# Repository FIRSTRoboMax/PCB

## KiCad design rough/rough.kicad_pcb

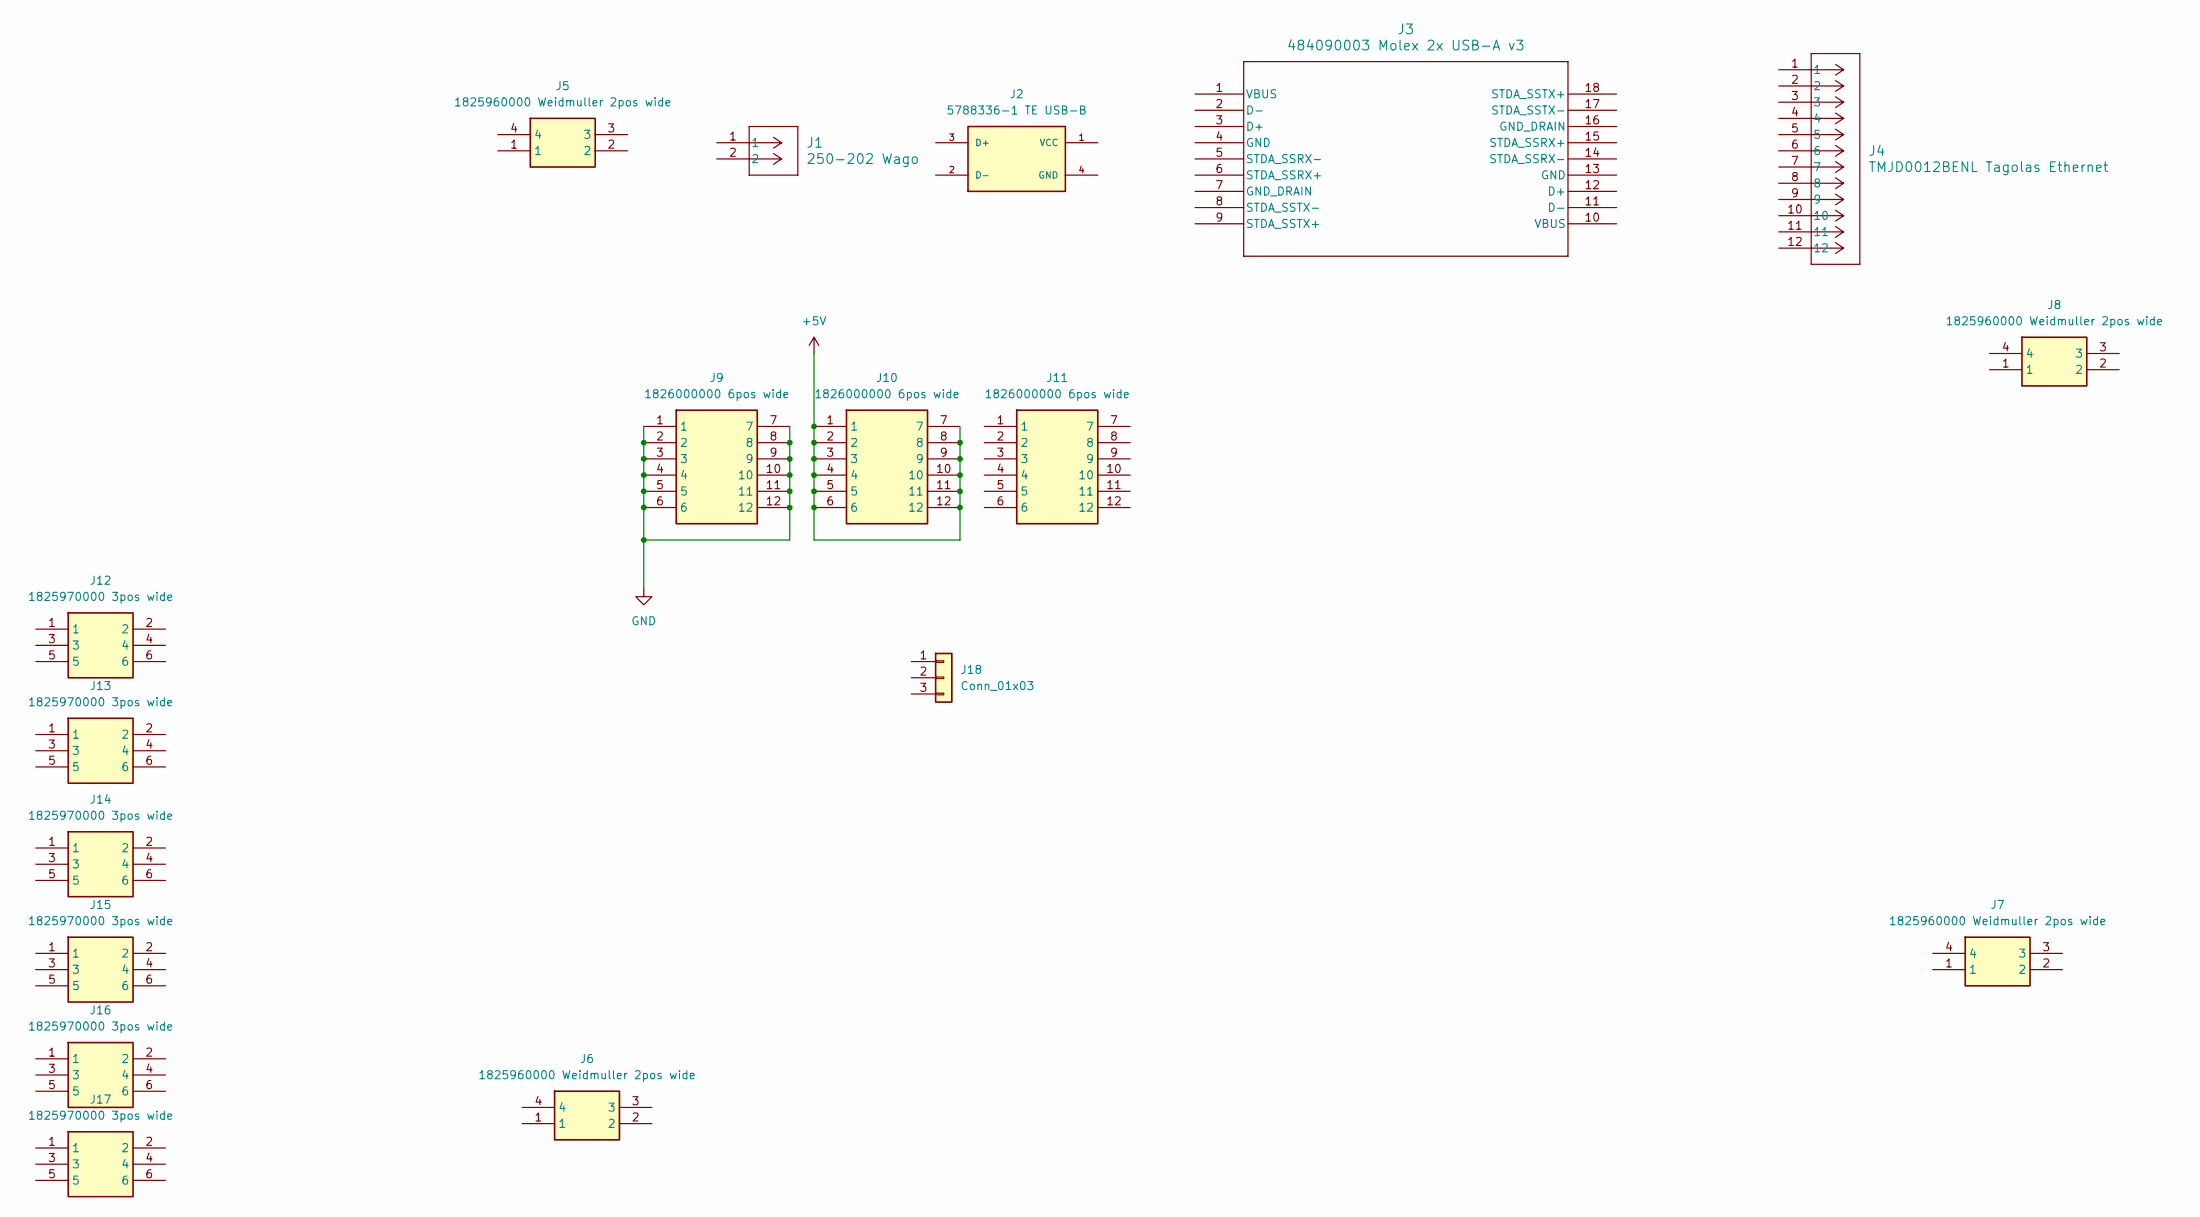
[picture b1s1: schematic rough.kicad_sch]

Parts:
J1: 250-202 Wago; CONN_250-202
J2: 5788336-1 TE USB-B; TE_5788336-1_USB-B; PARTREV R
J3: 484090003 Molex 2x USB-A v3; 48409-0003_MOL
J4: TMJD0012BENL Tagolas Ethernet; CONN12_0012BENL_TAL
J5, J6, J7, J8: 1825960000 Weidmuller 2pos wide; 1825960000; Manufacturer_Part_Number 1825960000; Mouser Part Number 470-1825960000
J9, J10, J11: 1826000000 6pos wide; 1826000000; Manufacturer_Part_Number 1826000000; Mouser Part Number 470-1826000000
J12, J13, J14, J15, J16, J17: 1825970000 3pos wide; 1825970000; Manufacturer_Part_Number 1825970000; Mouser Part Number 470-1825970000
J18: Conn_01x03

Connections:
+5V: J10.1, J10.2, J10.3, J10.4, J10.5, J10.6, J10.7, J10.8, J10.9, J10.10, J10.11, J10.12
GND: J9.1, J9.2, J9.3, J9.4, J9.5, J9.6, J9.7, J9.8, J9.9, J9.10, J9.11, J9.12

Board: 2 copper layers, 17 parts (0 on the bottom side), 2 nets, no tracks yet.

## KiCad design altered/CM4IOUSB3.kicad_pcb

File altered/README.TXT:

These files have been created in version 6 of KiCAD.

Some of the 3d models need to be downloaded form the following places and put into the CM4IO.3shapes directory some models are approximations.

https://datasheets.raspberrypi.org/cm4/CM4-step.zip
https://www.te.com/global-en/product-171826-4.html
https://www.molex.com/molex/products/part-detail/memory_card_socket/5033981892

The models provided in the 3dmodels directory are from various manufacturers including Diodes, Hirose, MTCONN, Toby, TRXCOM. Terms and conditions for the use of the models remain with the original manufacture.

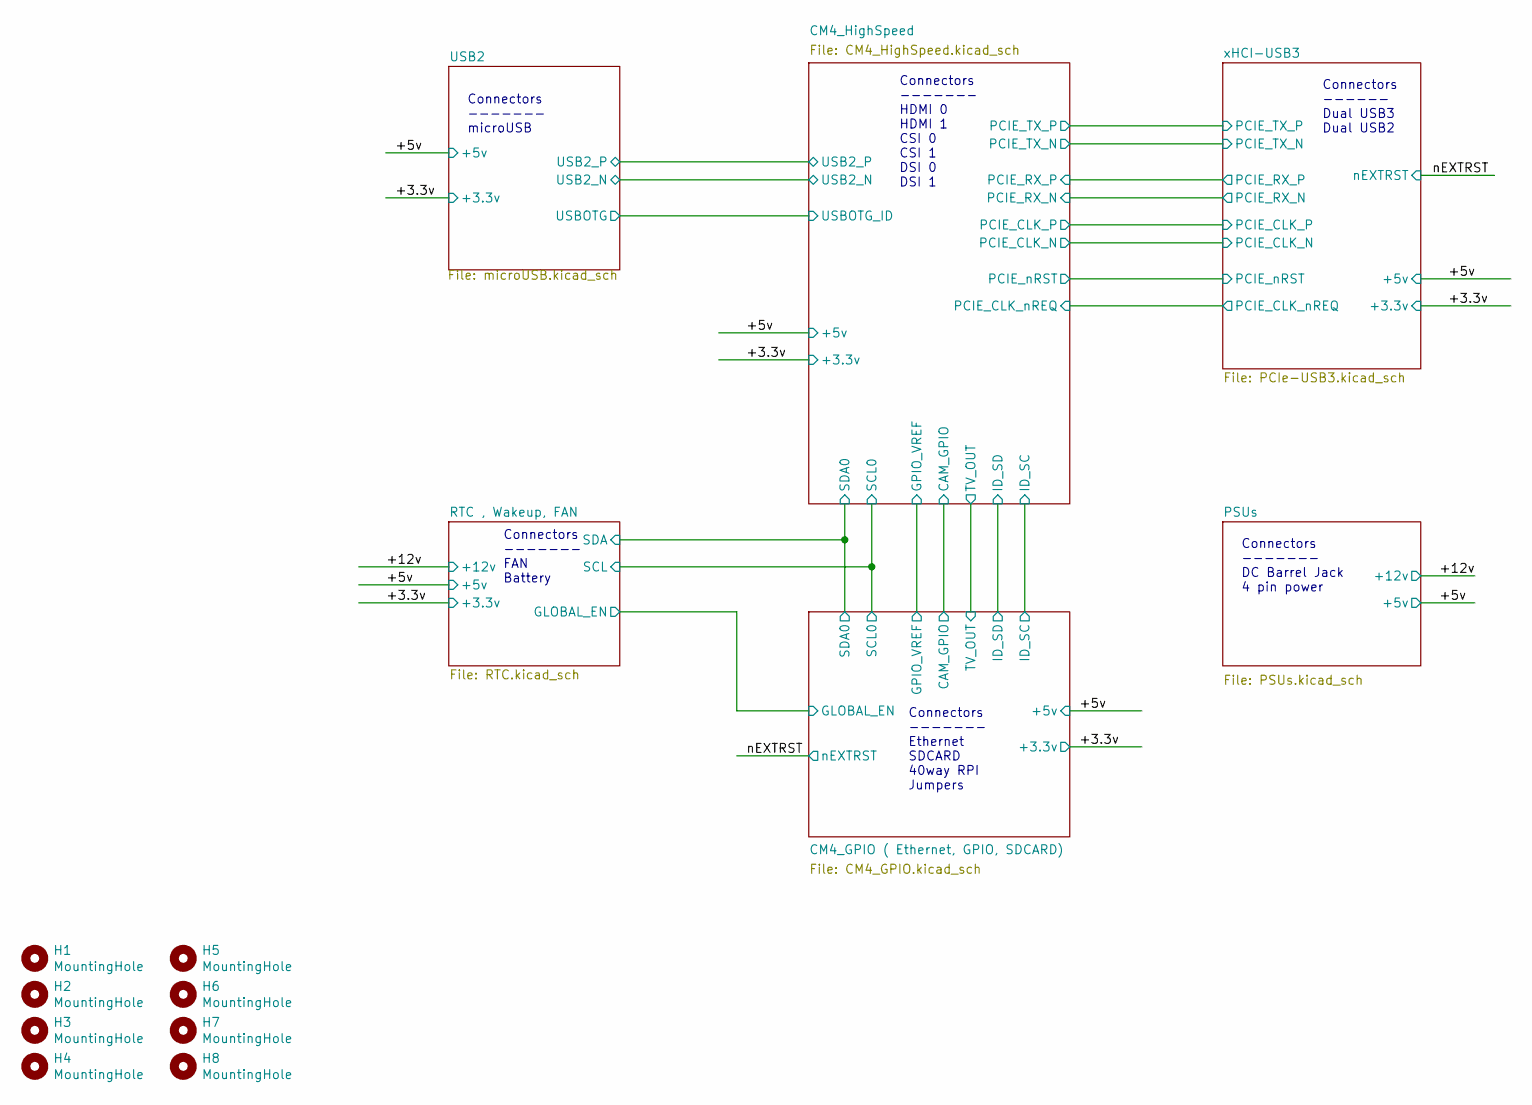
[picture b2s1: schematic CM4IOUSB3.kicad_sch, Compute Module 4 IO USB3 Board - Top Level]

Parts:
H1, H2, H3, H4, H5, H6, H7, H8: MountingHole; MountingHole_2.7mm_M2.5; Part Description M2.5 mounting hole

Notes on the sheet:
Connectors ------- microUSB
Connectors ------- DC Barrel Jack 4 pin power
Connectors ------- Ethernet SDCARD 40way RPI Jumpers
Connectors ------ Dual USB3 Dual USB2
Connectors ------- HDMI 0 HDMI 1 CSI 0 CSI 1 DSI 0 DSI 1
Connectors ------- FAN Battery

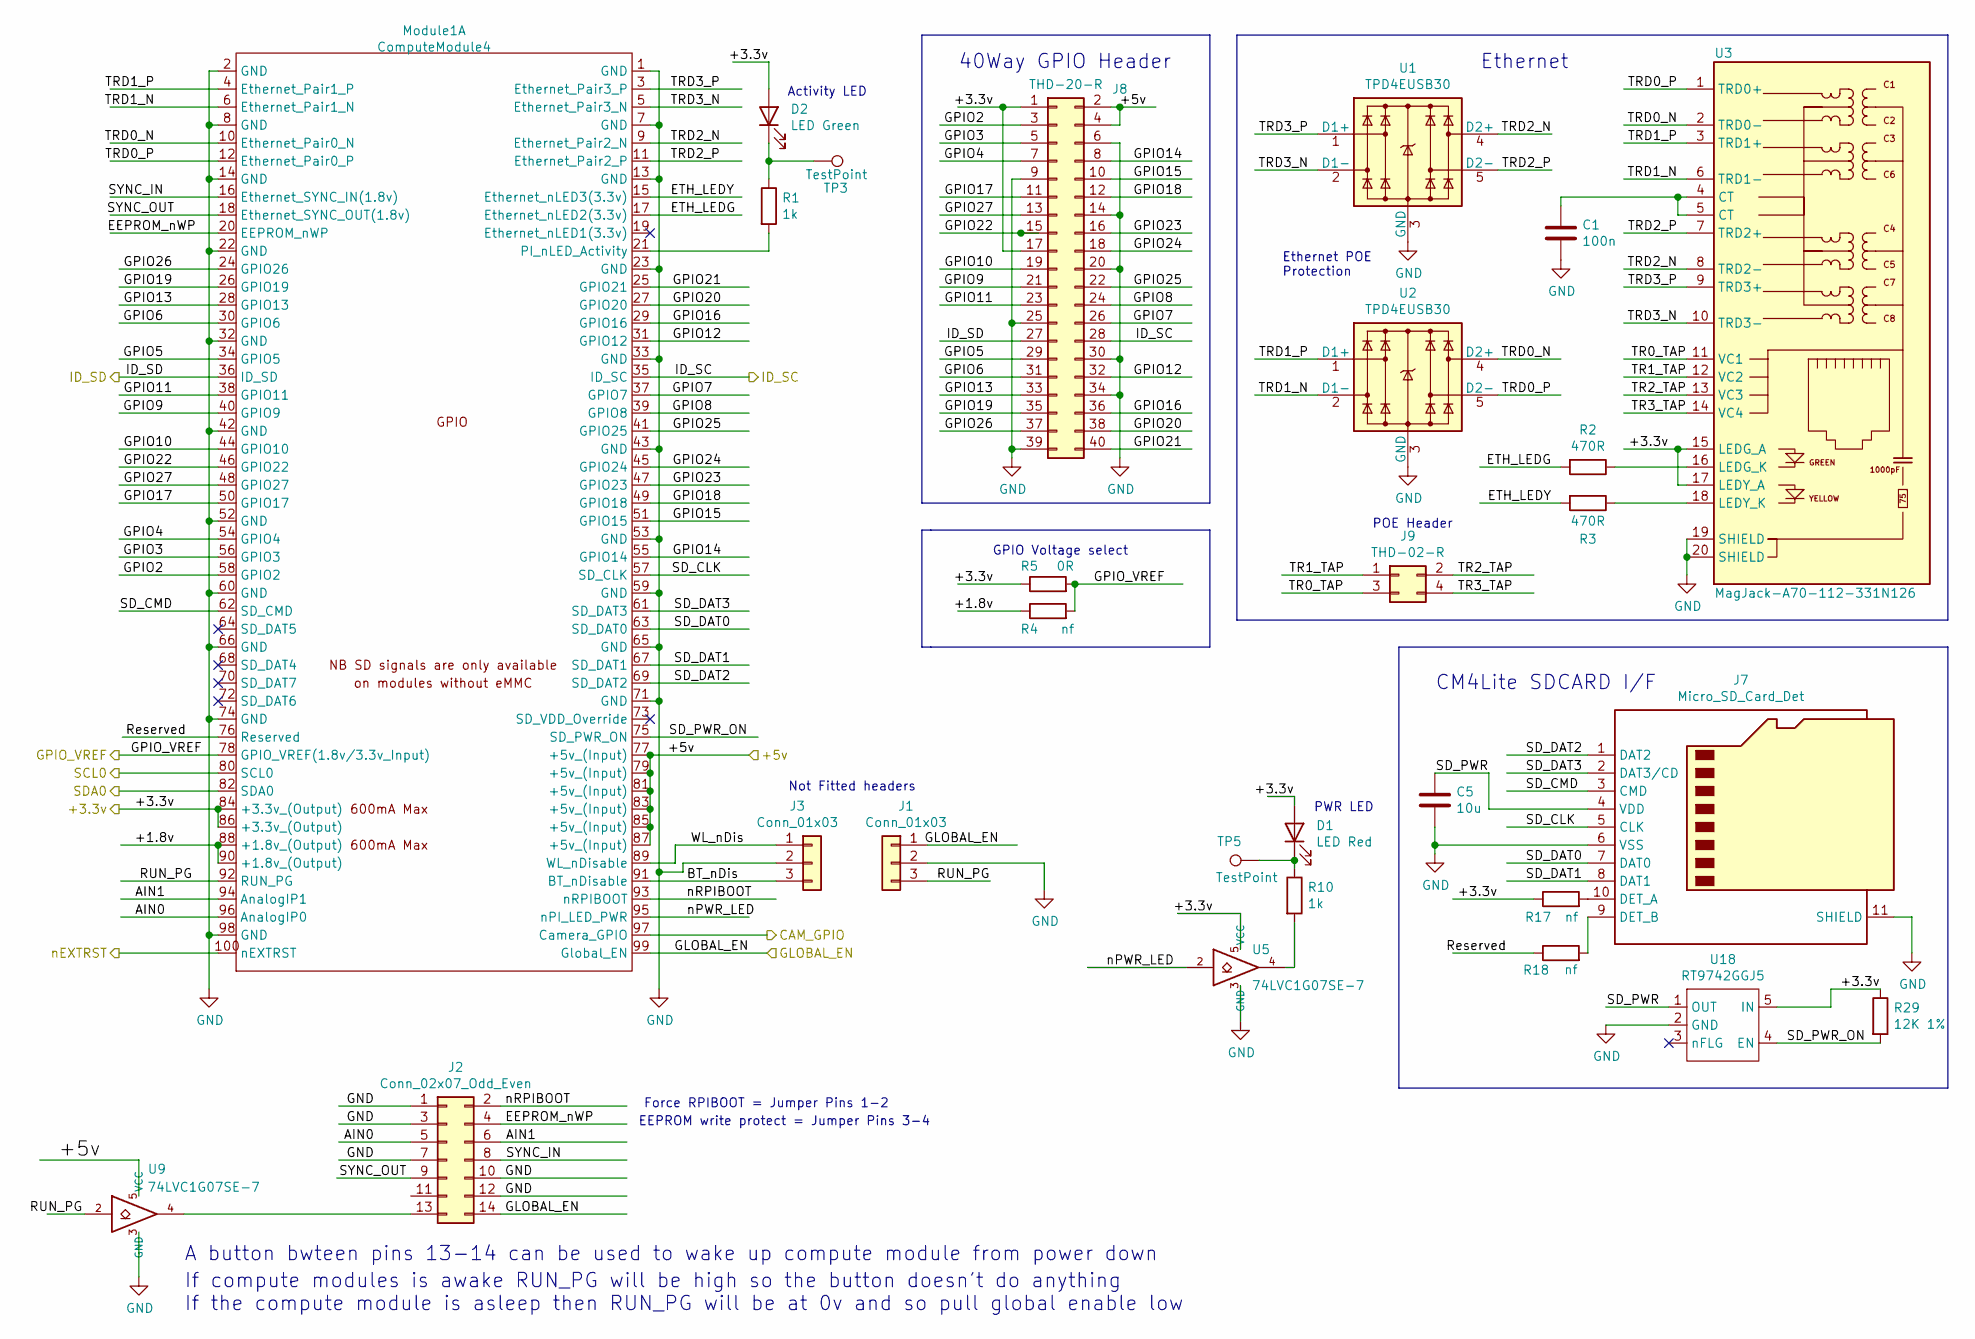
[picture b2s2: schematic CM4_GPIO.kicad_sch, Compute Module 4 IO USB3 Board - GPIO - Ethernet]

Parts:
C1: 100n; C_0402_1005Metric; Part Description 0.1uF 10% 16V Ceramic Capacitor X7R 040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
C5: 10u; C_0805_2012Metric; Part Description 10uF 10% 10V Ceramic Capacitor X7R 0805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
D1: LED Red; LED_0603_1608Metric; Part Description Red 620nm LED Indication - Discrete 2.2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
D2: LED Green; LED_0603_1608Metric; Part Description Green 572nm LED Indication - Discrete 2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
J1, J3: Conn_01x03; PinHeader_1x03_P2.54mm_Vertical; Part Description 3pin 0.1" connector
J2: Conn_02x07_Odd_Even; PinHeader_2x07_P2.54mm_Vertical; Part Description PinHeader_2x07_P2.54mm_Vertical
J7: Micro_SD_Card_Det; SDCARD_MOLEX_503398-1892; Part Description 9 (8 + 1) Position Card Connector micro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
J8: THD-20-R; PinHeader_2x20_P2.54mm_Vertical; Part Description PinHeader_2x20_P2.54mm_Vertical
J9: THD-02-R; PinHeader_2x02_P2.54mm_Vertical; Part Description PinHeader_2x02_P2.54mm_Vertical
Module1: ComputeModule4; Raspberry-Pi-4-Compute-Module; Part Description 100 Position Connector Receptacle, Cent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
R1, R10: 1k; R_0402_1005Metric; Part Description Resistor 1K M1005 1% 63mW
R2, R3: 470R; R_0402_1005Metric; Part Description Resistor 470R M1005 1% 63mW
R4: nf; R_0805_2012Metric_Pad1.15x1.40mm_HandSolder
R5: 0R; R_0805_2012Metric_Pad1.15x1.40mm_HandSolder; Part Description Resistor 0R M2012 5%
R17, R18: nf; R_0402_1005Metric; Part Description Resistor 1K M1005 1% 63mW
R29: 12K 1%; R_0402_1005Metric; Part Description Resistor 12K M1005 1% 63mW
TP3, TP5: TestPoint; TestPoint_Pad_2.0x2.0mm
U1, U2: TPD4EUSB30; USON-10_2.5x1.0mm_P0.5mm; Part Description Quad TVS diode for high speed signals (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
U3: MagJack-A70-112-331N126; TRJG0926HENL; Part Description Gigabit Ethernet Magjack
U5, U9: 74LVC1G07SE-7; SOT-353_SC-70-5; Part Description Buffer, Non-Inverting 1 Element 1 Bit p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
U18: RT9742GGJ5; SOT-23-5; Part Description Power Switch/Driver 1:1 N-Channel 1A TS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

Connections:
/+3.3v: D1.2 (A), D2.2 (A), J8.1, J8.17, Module1.84 (+3.3v_(Output)), Module1.86 (+3.3v_(Output)), R5.1, R17.1, R29.1, U3.15 (LEDG_A), U3.17 (LEDY_A), U5.5 (VCC), U18.5 (IN); also elsewhere on the board
/+5v: J8.2, J8.4, Module1.77 (+5v_(Input)), Module1.79 (+5v_(Input)), Module1.81 (+5v_(Input)), Module1.83 (+5v_(Input)), Module1.85 (+5v_(Input)), Module1.87 (+5v_(Input)), U9.5 (VCC); also elsewhere on the board
/CM4_GPIO ( Ethernet, GPIO, SDCARD)/+1.8v: Module1.88 (+1.8v_(Output)), Module1.90 (+1.8v_(Output)), R4.1
/CM4_GPIO ( Ethernet, GPIO, SDCARD)/AIN0: J2.5, Module1.96 (AnalogIP0)
/CM4_GPIO ( Ethernet, GPIO, SDCARD)/AIN1: J2.6, Module1.94 (AnalogIP1)
/CM4_GPIO ( Ethernet, GPIO, SDCARD)/BT_nDis: J3.3, Module1.91 (BT_nDisable)
/CM4_GPIO ( Ethernet, GPIO, SDCARD)/CAM_GPIO: Module1.97 (Camera_GPIO)
/CM4_GPIO ( Ethernet, GPIO, SDCARD)/EEPROM_nWP: J2.4, Module1.20 (EEPROM_nWP)
/CM4_GPIO ( Ethernet, GPIO, SDCARD)/ETH_LEDG: Module1.17 (Ethernet_nLED2(3.3v)), R2.2
/CM4_GPIO ( Ethernet, GPIO, SDCARD)/ETH_LEDY: Module1.15 (Ethernet_nLED3(3.3v)), R3.2
/CM4_GPIO ( Ethernet, GPIO, SDCARD)/GLOBAL_EN: J1.1, J2.14, Module1.99 (Global_EN); also elsewhere on the board
/CM4_GPIO ( Ethernet, GPIO, SDCARD)/GPIO2: J8.3, Module1.58 (GPIO2)
/CM4_GPIO ( Ethernet, GPIO, SDCARD)/GPIO3: J8.5, Module1.56 (GPIO3)
/CM4_GPIO ( Ethernet, GPIO, SDCARD)/GPIO4: J8.7, Module1.54 (GPIO4)
/CM4_GPIO ( Ethernet, GPIO, SDCARD)/GPIO5: J8.29, Module1.34 (GPIO5)
/CM4_GPIO ( Ethernet, GPIO, SDCARD)/GPIO6: J8.31, Module1.30 (GPIO6)
/CM4_GPIO ( Ethernet, GPIO, SDCARD)/GPIO7: J8.26, Module1.37 (GPIO7)
/CM4_GPIO ( Ethernet, GPIO, SDCARD)/GPIO8: J8.24, Module1.39 (GPIO8)
/CM4_GPIO ( Ethernet, GPIO, SDCARD)/GPIO9: J8.21, Module1.40 (GPIO9)
/CM4_GPIO ( Ethernet, GPIO, SDCARD)/GPIO10: J8.19, Module1.44 (GPIO10)
/CM4_GPIO ( Ethernet, GPIO, SDCARD)/GPIO11: J8.23, Module1.38 (GPIO11)
/CM4_GPIO ( Ethernet, GPIO, SDCARD)/GPIO12: J8.32, Module1.31 (GPIO12)
/CM4_GPIO ( Ethernet, GPIO, SDCARD)/GPIO13: J8.33, Module1.28 (GPIO13)
/CM4_GPIO ( Ethernet, GPIO, SDCARD)/GPIO14: J8.8, Module1.55 (GPIO14)
/CM4_GPIO ( Ethernet, GPIO, SDCARD)/GPIO15: J8.10, Module1.51 (GPIO15)
/CM4_GPIO ( Ethernet, GPIO, SDCARD)/GPIO16: J8.36, Module1.29 (GPIO16)
/CM4_GPIO ( Ethernet, GPIO, SDCARD)/GPIO17: J8.11, Module1.50 (GPIO17)
/CM4_GPIO ( Ethernet, GPIO, SDCARD)/GPIO18: J8.12, Module1.49 (GPIO18)
/CM4_GPIO ( Ethernet, GPIO, SDCARD)/GPIO19: J8.35, Module1.26 (GPIO19)
/CM4_GPIO ( Ethernet, GPIO, SDCARD)/GPIO20: J8.38, Module1.27 (GPIO20)
/CM4_GPIO ( Ethernet, GPIO, SDCARD)/GPIO21: J8.40, Module1.25 (GPIO21)
/CM4_GPIO ( Ethernet, GPIO, SDCARD)/GPIO22: J8.15, Module1.46 (GPIO22)
/CM4_GPIO ( Ethernet, GPIO, SDCARD)/GPIO23: J8.16, Module1.47 (GPIO23)
/CM4_GPIO ( Ethernet, GPIO, SDCARD)/GPIO24: J8.18, Module1.45 (GPIO24)
/CM4_GPIO ( Ethernet, GPIO, SDCARD)/GPIO25: J8.22, Module1.41 (GPIO25)
/CM4_GPIO ( Ethernet, GPIO, SDCARD)/GPIO26: J8.37, Module1.24 (GPIO26)
/CM4_GPIO ( Ethernet, GPIO, SDCARD)/GPIO27: J8.13, Module1.48 (GPIO27)
/CM4_GPIO ( Ethernet, GPIO, SDCARD)/GPIO_VREF: Module1.78 (GPIO_VREF(1.8v/3.3v_Input)), R4.2, R5.2
/CM4_GPIO ( Ethernet, GPIO, SDCARD)/ID_SC: J8.28, Module1.35 (ID_SC)
/CM4_GPIO ( Ethernet, GPIO, SDCARD)/ID_SD: J8.27, Module1.36 (ID_SD)
/CM4_GPIO ( Ethernet, GPIO, SDCARD)/RUN_PG: J1.3, Module1.92 (RUN_PG), U9.2
/CM4_GPIO ( Ethernet, GPIO, SDCARD)/Reserved: Module1.76 (Reserved), R18.1
/CM4_GPIO ( Ethernet, GPIO, SDCARD)/SD_CLK: J7.5 (CLK), Module1.57 (SD_CLK)
/CM4_GPIO ( Ethernet, GPIO, SDCARD)/SD_CMD: J7.3 (CMD), Module1.62 (SD_CMD)
/CM4_GPIO ( Ethernet, GPIO, SDCARD)/SD_DAT0: J7.7 (DAT0), Module1.63 (SD_DAT0)
/CM4_GPIO ( Ethernet, GPIO, SDCARD)/SD_DAT1: J7.8 (DAT1), Module1.67 (SD_DAT1)
/CM4_GPIO ( Ethernet, GPIO, SDCARD)/SD_DAT2: J7.1 (DAT2), Module1.69 (SD_DAT2)
/CM4_GPIO ( Ethernet, GPIO, SDCARD)/SD_DAT3: J7.2 (DAT3/CD), Module1.61 (SD_DAT3)
/CM4_GPIO ( Ethernet, GPIO, SDCARD)/SD_PWR: C5.1, J7.4 (VDD), U18.1 (OUT)
/CM4_GPIO ( Ethernet, GPIO, SDCARD)/SD_PWR_ON: Module1.75 (SD_PWR_ON), R29.2, U18.4 (EN)
/CM4_GPIO ( Ethernet, GPIO, SDCARD)/SYNC_IN: J2.8, Module1.16 (Ethernet_SYNC_IN(1.8v))
/CM4_GPIO ( Ethernet, GPIO, SDCARD)/SYNC_OUT: J2.9, Module1.18 (Ethernet_SYNC_OUT(1.8v))
/CM4_GPIO ( Ethernet, GPIO, SDCARD)/TR0_TAP: J9.3, U3.11 (VC1)
/CM4_GPIO ( Ethernet, GPIO, SDCARD)/TR1_TAP: J9.1, U3.12 (VC2)
/CM4_GPIO ( Ethernet, GPIO, SDCARD)/TR2_TAP: J9.2, U3.13 (VC3)
/CM4_GPIO ( Ethernet, GPIO, SDCARD)/TR3_TAP: J9.4, U3.14 (VC4)
/CM4_GPIO ( Ethernet, GPIO, SDCARD)/TRD0_N: Module1.10 (Ethernet_Pair0_N), U2.4 (D2+), U2.7, U3.2 (TRD0-)
/CM4_GPIO ( Ethernet, GPIO, SDCARD)/TRD0_P: Module1.12 (Ethernet_Pair0_P), U2.5 (D2-), U2.6, U3.1 (TRD0+)
/CM4_GPIO ( Ethernet, GPIO, SDCARD)/TRD1_N: Module1.6 (Ethernet_Pair1_N), U2.2 (D1-), U2.9, U3.6 (TRD1-)
/CM4_GPIO ( Ethernet, GPIO, SDCARD)/TRD1_P: Module1.4 (Ethernet_Pair1_P), U2.1 (D1+), U2.10, U3.3 (TRD1+)
/CM4_GPIO ( Ethernet, GPIO, SDCARD)/TRD2_N: Module1.9 (Ethernet_Pair2_N), U1.4 (D2+), U1.7, U3.8 (TRD2-)
/CM4_GPIO ( Ethernet, GPIO, SDCARD)/TRD2_P: Module1.11 (Ethernet_Pair2_P), U1.5 (D2-), U1.6, U3.7 (TRD2+)
/CM4_GPIO ( Ethernet, GPIO, SDCARD)/TRD3_N: Module1.5 (Ethernet_Pair3_N), U1.2 (D1-), U1.9, U3.10 (TRD3-)
/CM4_GPIO ( Ethernet, GPIO, SDCARD)/TRD3_P: Module1.3 (Ethernet_Pair3_P), U1.1 (D1+), U1.10, U3.9 (TRD3+)
/CM4_GPIO ( Ethernet, GPIO, SDCARD)/WL_nDis: J3.1, Module1.89 (WL_nDisable)
/CM4_GPIO ( Ethernet, GPIO, SDCARD)/nPWR_LED: Module1.95 (nPI_LED_PWR), U5.2
/CM4_GPIO ( Ethernet, GPIO, SDCARD)/nRPIBOOT: J2.2, Module1.93 (nRPIBOOT)
/RTC , Wakeup, FAN/SCL: Module1.80 (SCL0); also elsewhere on the board
/RTC , Wakeup, FAN/SDA: Module1.82 (SDA0); also elsewhere on the board
/nEXTRST: Module1.100 (nEXTRST); also elsewhere on the board
GND: C1.2, C5.2, J1.2, J2.1, J2.3, J2.7, J2.10, J2.12, J3.2, J7.6 (VSS), J7.11 (SHIELD), J8.6, J8.9, J8.14, J8.20, J8.25, J8.30, J8.34, J8.39, Module1.1 (GND), Module1.2 (GND), Module1.7 (GND), Module1.8 (GND), Module1.13 (GND), Module1.14 (GND), Module1.22 (GND), Module1.23 (GND), Module1.32 (GND), Module1.33 (GND), Module1.42 (GND), Module1.43 (GND), Module1.52 (GND), Module1.53 (GND), Module1.59 (GND), Module1.60 (GND), Module1.65 (GND), Module1.66 (GND), Module1.71 (GND), Module1.74 (GND), Module1.98 (GND), U1.3 (GND), U1.8 (GND), U2.3 (GND), U2.8 (GND), U3.19 (SHIELD), U3.20 (SHIELD), U5.3 (GND), U9.3 (GND), U18.2 (GND); also elsewhere on the board
unnamed: C1.1, U3.4 (CT), U3.5 (CT)
unnamed: D1.1 (K), R10.1, TP5.1
unnamed: D2.1 (K), R1.1, TP3.1
unnamed: J2.13, U9.4
unnamed: J7.10 (DET_A), R17.2
unnamed: J7.9 (DET_B), R18.2
unnamed: Module1.21 (PI_nLED_Activity), R1.2
unnamed: R10.2, U5.4
unnamed: R2.1, U3.16 (LEDG_K)
unnamed: R3.1, U3.18 (LEDY_K)

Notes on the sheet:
40Way GPIO Header
Activity LED
Ethernet POE Protection
GPIO Voltage select
EEPROM write protect = Jumper Pins 3-4
Not Fitted headers
POE Header
Force RPIBOOT = Jumper Pins 1-2
PWR LED
A button bwteen pins 13-14 can be used to wake up compute module from power down
Ethernet
If compute modules is awake RUN_PG will be high so the button doesn't do anything If the compute module is asleep then RUN_PG will be at 0v and so pull global enable low
CM4Lite SDCARD I/F

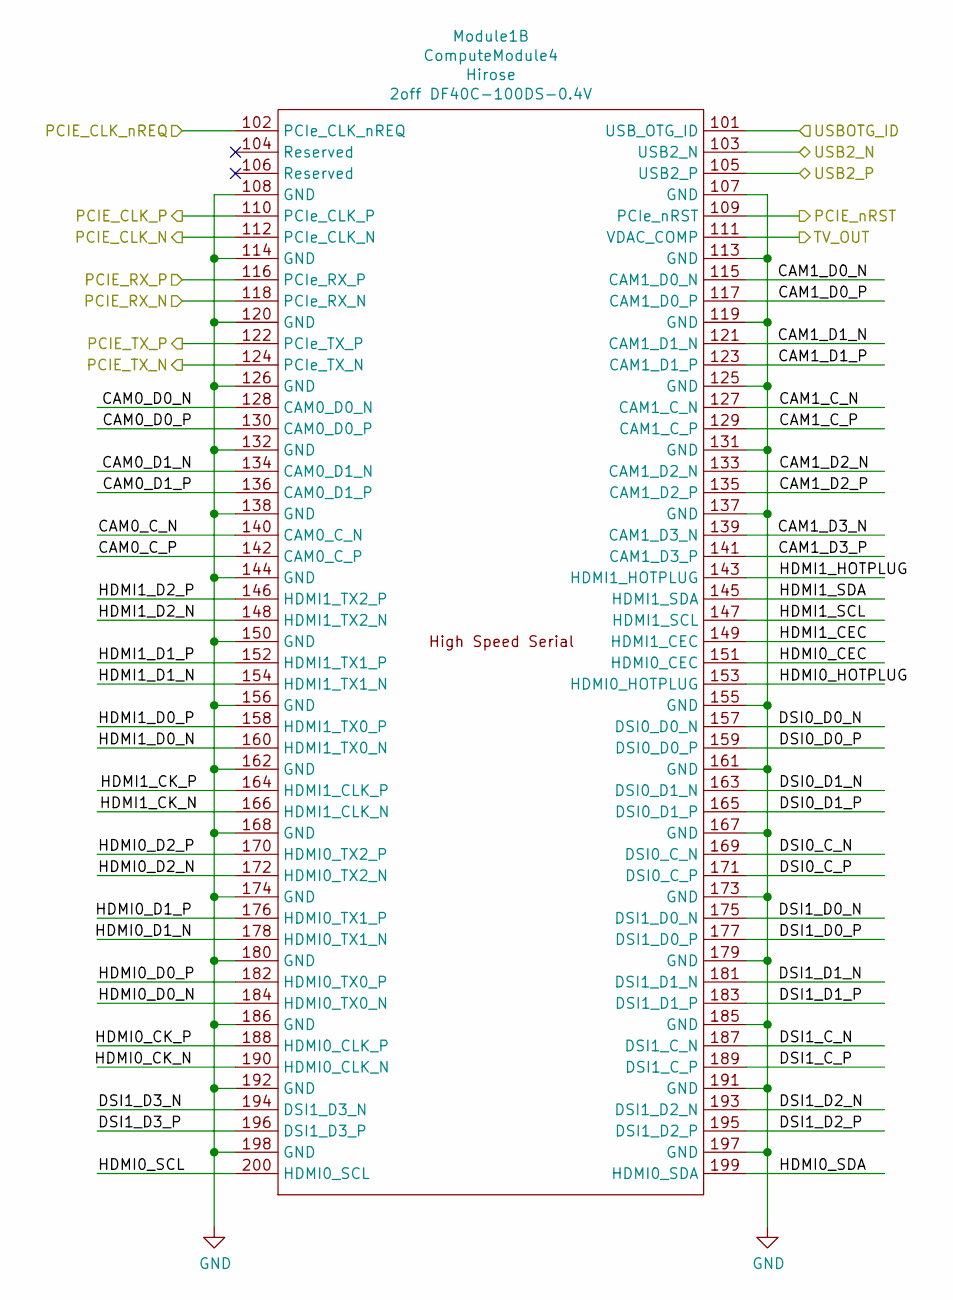
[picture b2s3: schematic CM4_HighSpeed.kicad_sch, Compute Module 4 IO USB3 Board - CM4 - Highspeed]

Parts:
Module1: ComputeModule4; Raspberry-Pi-4-Compute-Module; Part Description 100 Position Connector Receptacle, Cent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

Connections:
/CM4_HighSpeed/CAM0_C_N: Module1.140 (CAM0_C_N)
/CM4_HighSpeed/CAM0_C_P: Module1.142 (CAM0_C_P)
/CM4_HighSpeed/CAM0_D0_N: Module1.128 (CAM0_D0_N)
/CM4_HighSpeed/CAM0_D0_P: Module1.130 (CAM0_D0_P)
/CM4_HighSpeed/CAM0_D1_N: Module1.134 (CAM0_D1_N)
/CM4_HighSpeed/CAM0_D1_P: Module1.136 (CAM0_D1_P)
/CM4_HighSpeed/CAM1_C_N: Module1.127 (CAM1_C_N)
/CM4_HighSpeed/CAM1_C_P: Module1.129 (CAM1_C_P)
/CM4_HighSpeed/CAM1_D0_N: Module1.115 (CAM1_D0_N)
/CM4_HighSpeed/CAM1_D0_P: Module1.117 (CAM1_D0_P)
/CM4_HighSpeed/CAM1_D1_N: Module1.121 (CAM1_D1_N)
/CM4_HighSpeed/CAM1_D1_P: Module1.123 (CAM1_D1_P)
/CM4_HighSpeed/CAM1_D2_N: Module1.133 (CAM1_D2_N)
/CM4_HighSpeed/CAM1_D2_P: Module1.135 (CAM1_D2_P)
/CM4_HighSpeed/CAM1_D3_N: Module1.139 (CAM1_D3_N)
/CM4_HighSpeed/CAM1_D3_P: Module1.141 (CAM1_D3_P)
/CM4_HighSpeed/DSI0_C_N: Module1.169 (DSI0_C_N)
/CM4_HighSpeed/DSI0_C_P: Module1.171 (DSI0_C_P)
/CM4_HighSpeed/DSI0_D0_N: Module1.157 (DSI0_D0_N)
/CM4_HighSpeed/DSI0_D0_P: Module1.159 (DSI0_D0_P)
/CM4_HighSpeed/DSI0_D1_N: Module1.163 (DSI0_D1_N)
/CM4_HighSpeed/DSI0_D1_P: Module1.165 (DSI0_D1_P)
/CM4_HighSpeed/DSI1_C_N: Module1.187 (DSI1_C_N)
/CM4_HighSpeed/DSI1_C_P: Module1.189 (DSI1_C_P)
/CM4_HighSpeed/DSI1_D0_N: Module1.175 (DSI1_D0_N)
/CM4_HighSpeed/DSI1_D0_P: Module1.177 (DSI1_D0_P)
/CM4_HighSpeed/DSI1_D1_N: Module1.181 (DSI1_D1_N)
/CM4_HighSpeed/DSI1_D1_P: Module1.183 (DSI1_D1_P)
/CM4_HighSpeed/DSI1_D2_N: Module1.193 (DSI1_D2_N)
/CM4_HighSpeed/DSI1_D2_P: Module1.195 (DSI1_D2_P)
/CM4_HighSpeed/DSI1_D3_N: Module1.194 (DSI1_D3_N)
/CM4_HighSpeed/DSI1_D3_P: Module1.196 (DSI1_D3_P)
/CM4_HighSpeed/HDMI0_CEC: Module1.151 (HDMI0_CEC)
/CM4_HighSpeed/HDMI0_CK_N: Module1.190 (HDMI0_CLK_N)
/CM4_HighSpeed/HDMI0_CK_P: Module1.188 (HDMI0_CLK_P)
/CM4_HighSpeed/HDMI0_D0_N: Module1.184 (HDMI0_TX0_N)
/CM4_HighSpeed/HDMI0_D0_P: Module1.182 (HDMI0_TX0_P)
/CM4_HighSpeed/HDMI0_D1_N: Module1.178 (HDMI0_TX1_N)
/CM4_HighSpeed/HDMI0_D1_P: Module1.176 (HDMI0_TX1_P)
/CM4_HighSpeed/HDMI0_D2_N: Module1.172 (HDMI0_TX2_N)
/CM4_HighSpeed/HDMI0_D2_P: Module1.170 (HDMI0_TX2_P)
/CM4_HighSpeed/HDMI0_HOTPLUG: Module1.153 (HDMI0_HOTPLUG)
/CM4_HighSpeed/HDMI0_SCL: Module1.200 (HDMI0_SCL)
/CM4_HighSpeed/HDMI0_SDA: Module1.199 (HDMI0_SDA)
/CM4_HighSpeed/HDMI1_CEC: Module1.149 (HDMI1_CEC)
/CM4_HighSpeed/HDMI1_CK_N: Module1.166 (HDMI1_CLK_N)
/CM4_HighSpeed/HDMI1_CK_P: Module1.164 (HDMI1_CLK_P)
/CM4_HighSpeed/HDMI1_D0_N: Module1.160 (HDMI1_TX0_N)
/CM4_HighSpeed/HDMI1_D0_P: Module1.158 (HDMI1_TX0_P)
/CM4_HighSpeed/HDMI1_D1_N: Module1.154 (HDMI1_TX1_N)
/CM4_HighSpeed/HDMI1_D1_P: Module1.152 (HDMI1_TX1_P)
/CM4_HighSpeed/HDMI1_D2_N: Module1.148 (HDMI1_TX2_N)
/CM4_HighSpeed/HDMI1_D2_P: Module1.146 (HDMI1_TX2_P)
/CM4_HighSpeed/HDMI1_HOTPLUG: Module1.143 (HDMI1_HOTPLUG)
/CM4_HighSpeed/HDMI1_SCL: Module1.147 (HDMI1_SCL)
/CM4_HighSpeed/HDMI1_SDA: Module1.145 (HDMI1_SDA)
/CM4_HighSpeed/PCIE_CLK_N: Module1.112 (PCIe_CLK_N); also elsewhere on the board
/CM4_HighSpeed/PCIE_CLK_P: Module1.110 (PCIe_CLK_P); also elsewhere on the board
/CM4_HighSpeed/PCIE_CLK_nREQ: Module1.102 (PCIe_CLK_nREQ); also elsewhere on the board
/CM4_HighSpeed/PCIE_RX_N: Module1.118 (PCIe_RX_N); also elsewhere on the board
/CM4_HighSpeed/PCIE_RX_P: Module1.116 (PCIe_RX_P); also elsewhere on the board
/CM4_HighSpeed/PCIE_TX_N: Module1.124 (PCIe_TX_N); also elsewhere on the board
/CM4_HighSpeed/PCIE_TX_P: Module1.122 (PCIe_TX_P); also elsewhere on the board
/CM4_HighSpeed/PCIE_nRST: Module1.109 (PCIe_nRST); also elsewhere on the board
/CM4_HighSpeed/TV_OUT: Module1.111 (VDAC_COMP)
/CM4_HighSpeed/USBOTG_ID: Module1.101 (USB_OTG_ID); also elsewhere on the board
/USB2/USBD_N: Module1.103 (USB2_N); also elsewhere on the board
/USB2/USBD_P: Module1.105 (USB2_P); also elsewhere on the board
GND: Module1.107 (GND), Module1.108 (GND), Module1.113 (GND), Module1.114 (GND), Module1.119 (GND), Module1.120 (GND), Module1.125 (GND), Module1.126 (GND), Module1.131 (GND), Module1.132 (GND), Module1.137 (GND), Module1.138 (GND), Module1.144 (GND), Module1.150 (GND), Module1.155 (GND), Module1.156 (GND), Module1.161 (GND), Module1.162 (GND), Module1.167 (GND), Module1.168 (GND), Module1.173 (GND), Module1.174 (GND), Module1.179 (GND), Module1.180 (GND), Module1.185 (GND), Module1.186 (GND), Module1.191 (GND), Module1.192 (GND), Module1.197 (GND), Module1.198 (GND); also elsewhere on the board

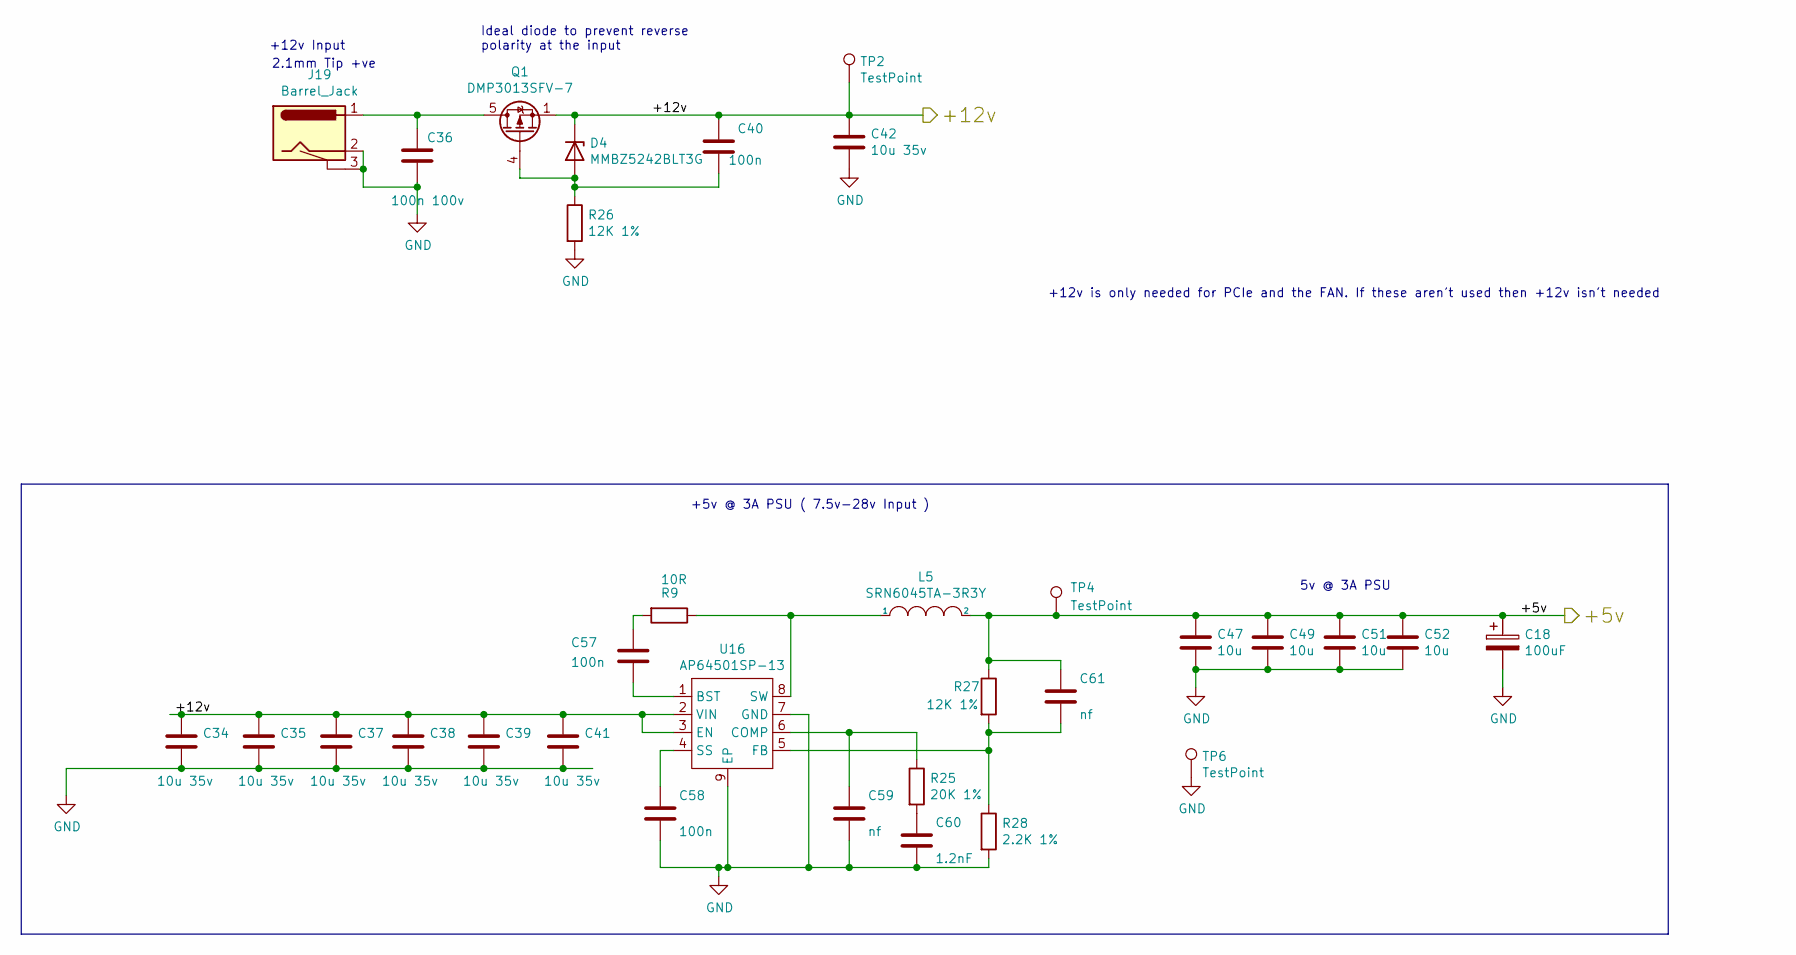
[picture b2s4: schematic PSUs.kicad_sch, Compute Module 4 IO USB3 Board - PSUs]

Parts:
C18: 100uF; CP_EIA-7343-31_Kemet-D; Part Description Capacitor, SP-Cap, 100u, 6.3V, 15mR ESR
C34, C35, C37, C38, C39, C41, C42: 10u 35v; C_0805_2012Metric; Part Description 10uF 10% or 20% 35V Ceramic Capacitor X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
C36: 100n 100v; C_0402_1005Metric; Part Description 0.1uF 10% 100V Ceramic Capacitor X5R 04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
C40, C57, C58: 100n; C_0402_1005Metric; Part Description 0.1uF 10% 16V Ceramic Capacitor X7R 040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
C47, C49, C51, C52: 10u; C_0805_2012Metric; Part Description 10uF 10% 10V Ceramic Capacitor X7R 0805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
C59: nf; C_0402_1005Metric
C60: 1.2nF; C_0402_1005Metric; Part Description 1200pF 10% 10V Ceramic Capacitor X5R 04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
C61: nf; C_0402_1005Metric; Part Description 220 pF, 50 V, 0402 [1005 Metric], ± 5%,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
D4: MMBZ5242BLT3G; D_SOT-23_ANK; Part Description Zener Diode 12V 225mW 5% Surface Mount 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
J19: Barrel_Jack; BarrelJack_Horizontal; Part Description DC Power Connectors PCB 2.1MM
L5: SRN6045TA-3R3Y; L_Bourns_SRN6045TA; Part Description 3.3µH Semi-Shielded Wirewound Inductor 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
Q1: DMP3013SFV-7; Diodes_PowerDI3333-8; Part Description DMP3013SFV-7 - Power MOSFET, P Channel,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
R9: 10R; R_0402_1005Metric; Part Description Resistor 10R M1005 1% 63mW
R25: 20K 1%; R_0402_1005Metric; Part Description Resistor 20K M1005 1% 63mW
R26, R27: 12K 1%; R_0402_1005Metric; Part Description Resistor 12K M1005 1% 63mW
R28: 2.2K 1%; R_0402_1005Metric; Part Description Resistor 2.2K M1005 1% 63mW
TP2, TP4, TP6: TestPoint; TestPoint_Pad_2.0x2.0mm
U16: AP64501SP-13; SOIC-8-1EP_3.9x4.9mm_P1.27mm_EP2.95x4.9mm_Mask2.71x3.4mm_Th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; Part Description Buck Switching Regulator IC Positive Ad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

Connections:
/+5v: C18.1, C47.1, C49.1, C51.1, C52.1, C61.1, L5.2, R27.1, TP4.1; also elsewhere on the board
/+12v: C34.1, C35.1, C37.1, C38.1, C39.1, C40.1, C41.1, C42.1, D4.1 (K), Q1.1 (S), Q1.2 (S), Q1.3 (S), TP2.1, U16.2 (VIN), U16.3 (EN)
GND: C18.2, C34.2, C35.2, C36.2, C37.2, C38.2, C39.2, C41.2, C42.2, C47.2, C49.2, C51.2, C52.2, C58.2, C59.2, C60.2, J19.2, J19.3, R26.2, R28.2, TP6.1, U16.7 (GND), U16.9 (EP); also elsewhere on the board
unnamed: C57.1, R9.2
unnamed: C60.1, R25.2
unnamed: C40.2, D4.2 (A), Q1.4 (G), R26.1
unnamed: C36.1, J19.1, Q1.5 (D)
unnamed: C57.2, U16.1 (BST)
unnamed: C59.1, R25.1, U16.6 (COMP)
unnamed: C61.2, R27.2, R28.1, U16.5 (FB)
unnamed: C58.1, U16.4 (SS)
unnamed: L5.1, R9.1, U16.8 (SW)

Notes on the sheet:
+5v @ 3A PSU ( 7.5v-28v Input )
+12v is only needed for PCIe and the FAN. If these aren't used then +12v isn't needed
Ideal diode to prevent reverse polarity at the input
+12v Input
2.1mm Tip +ve
5v @ 3A PSU

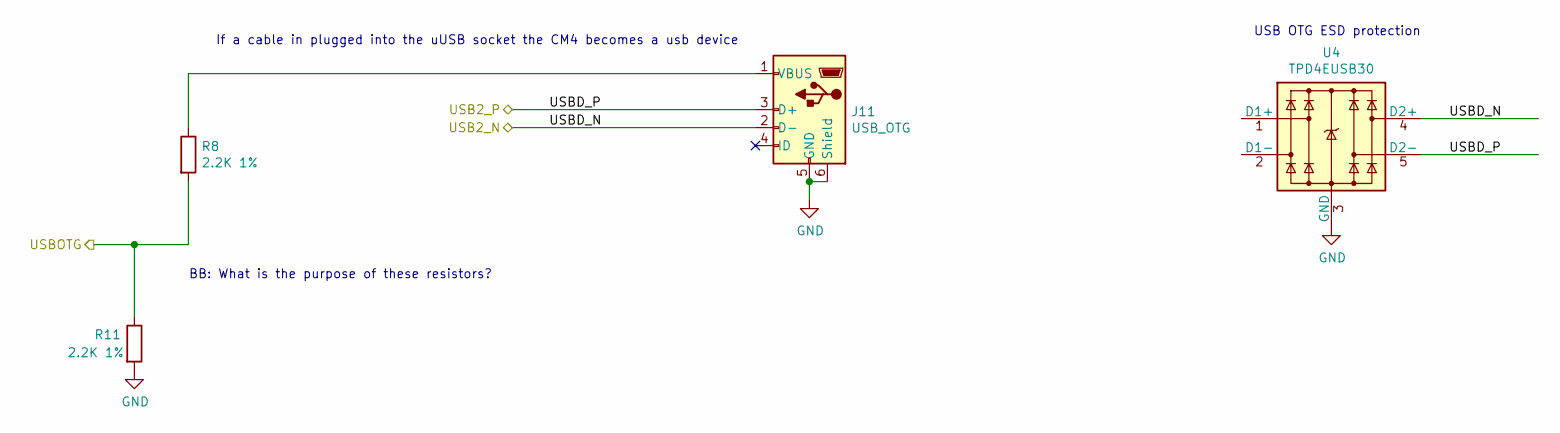
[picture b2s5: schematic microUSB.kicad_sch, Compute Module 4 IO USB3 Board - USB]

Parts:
J11: USB_OTG; USB_Micro-B_EDAC_UCON00686; Part Description USB - micro B USB 2.0 Receptacle Connec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
R8, R11: 2.2K 1%; R_0402_1005Metric; Part Description Resistor 2.2K M1005 1% 63mW
U4: TPD4EUSB30; USON-10_2.5x1.0mm_P0.5mm; Part Description Quad TVS diode for high speed signals (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

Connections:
/CM4_HighSpeed/USBOTG_ID: R8.2, R11.1; also elsewhere on the board
/USB2/USBD_N: J11.2 (D-), U4.4 (D2+), U4.7; also elsewhere on the board
/USB2/USBD_P: J11.3 (D+), U4.5 (D2-), U4.6; also elsewhere on the board
GND: J11.5 (GND), J11.6 (Shield), R11.2, U4.3 (GND), U4.8 (GND); also elsewhere on the board
unnamed: J11.1 (VBUS), R8.1
unnamed: U4.1 (D1+), U4.10
unnamed: U4.2 (D1-), U4.9

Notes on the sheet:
BB: What is the purpose of these resistors?
If a cable in plugged into the uUSB socket the CM4 becomes a usb device
USB OTG ESD protection

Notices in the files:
CM4IOUSB3.kicad_sch:
Copyright © 2020-2022 Raspberry Pi Ltd (formerly Raspberry Pi (Trading) Ltd.)
